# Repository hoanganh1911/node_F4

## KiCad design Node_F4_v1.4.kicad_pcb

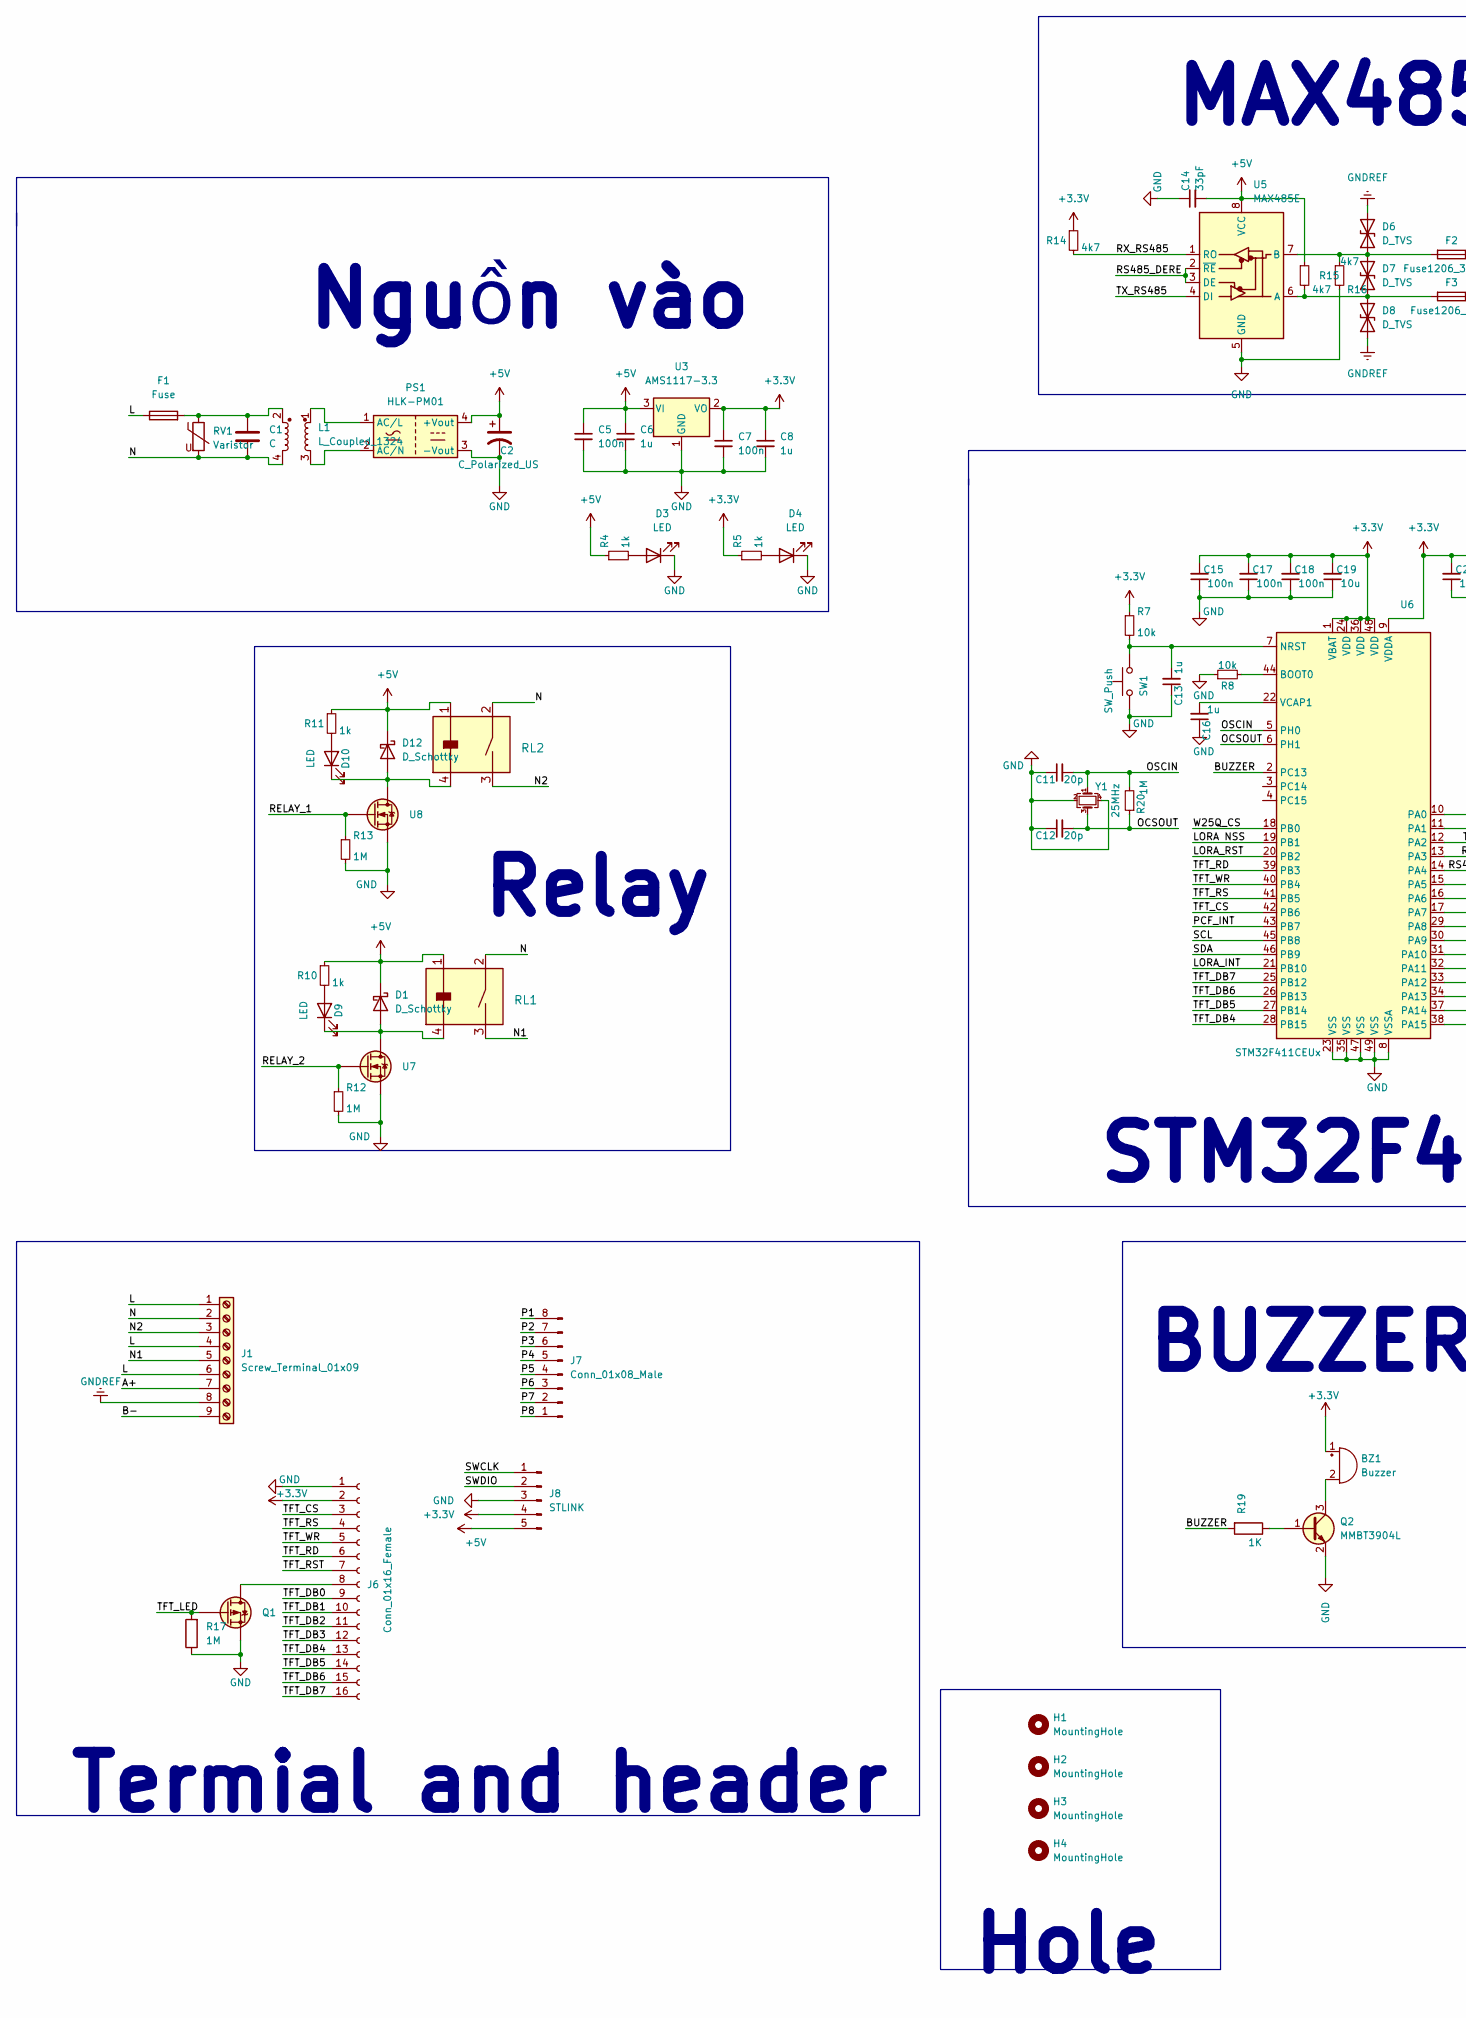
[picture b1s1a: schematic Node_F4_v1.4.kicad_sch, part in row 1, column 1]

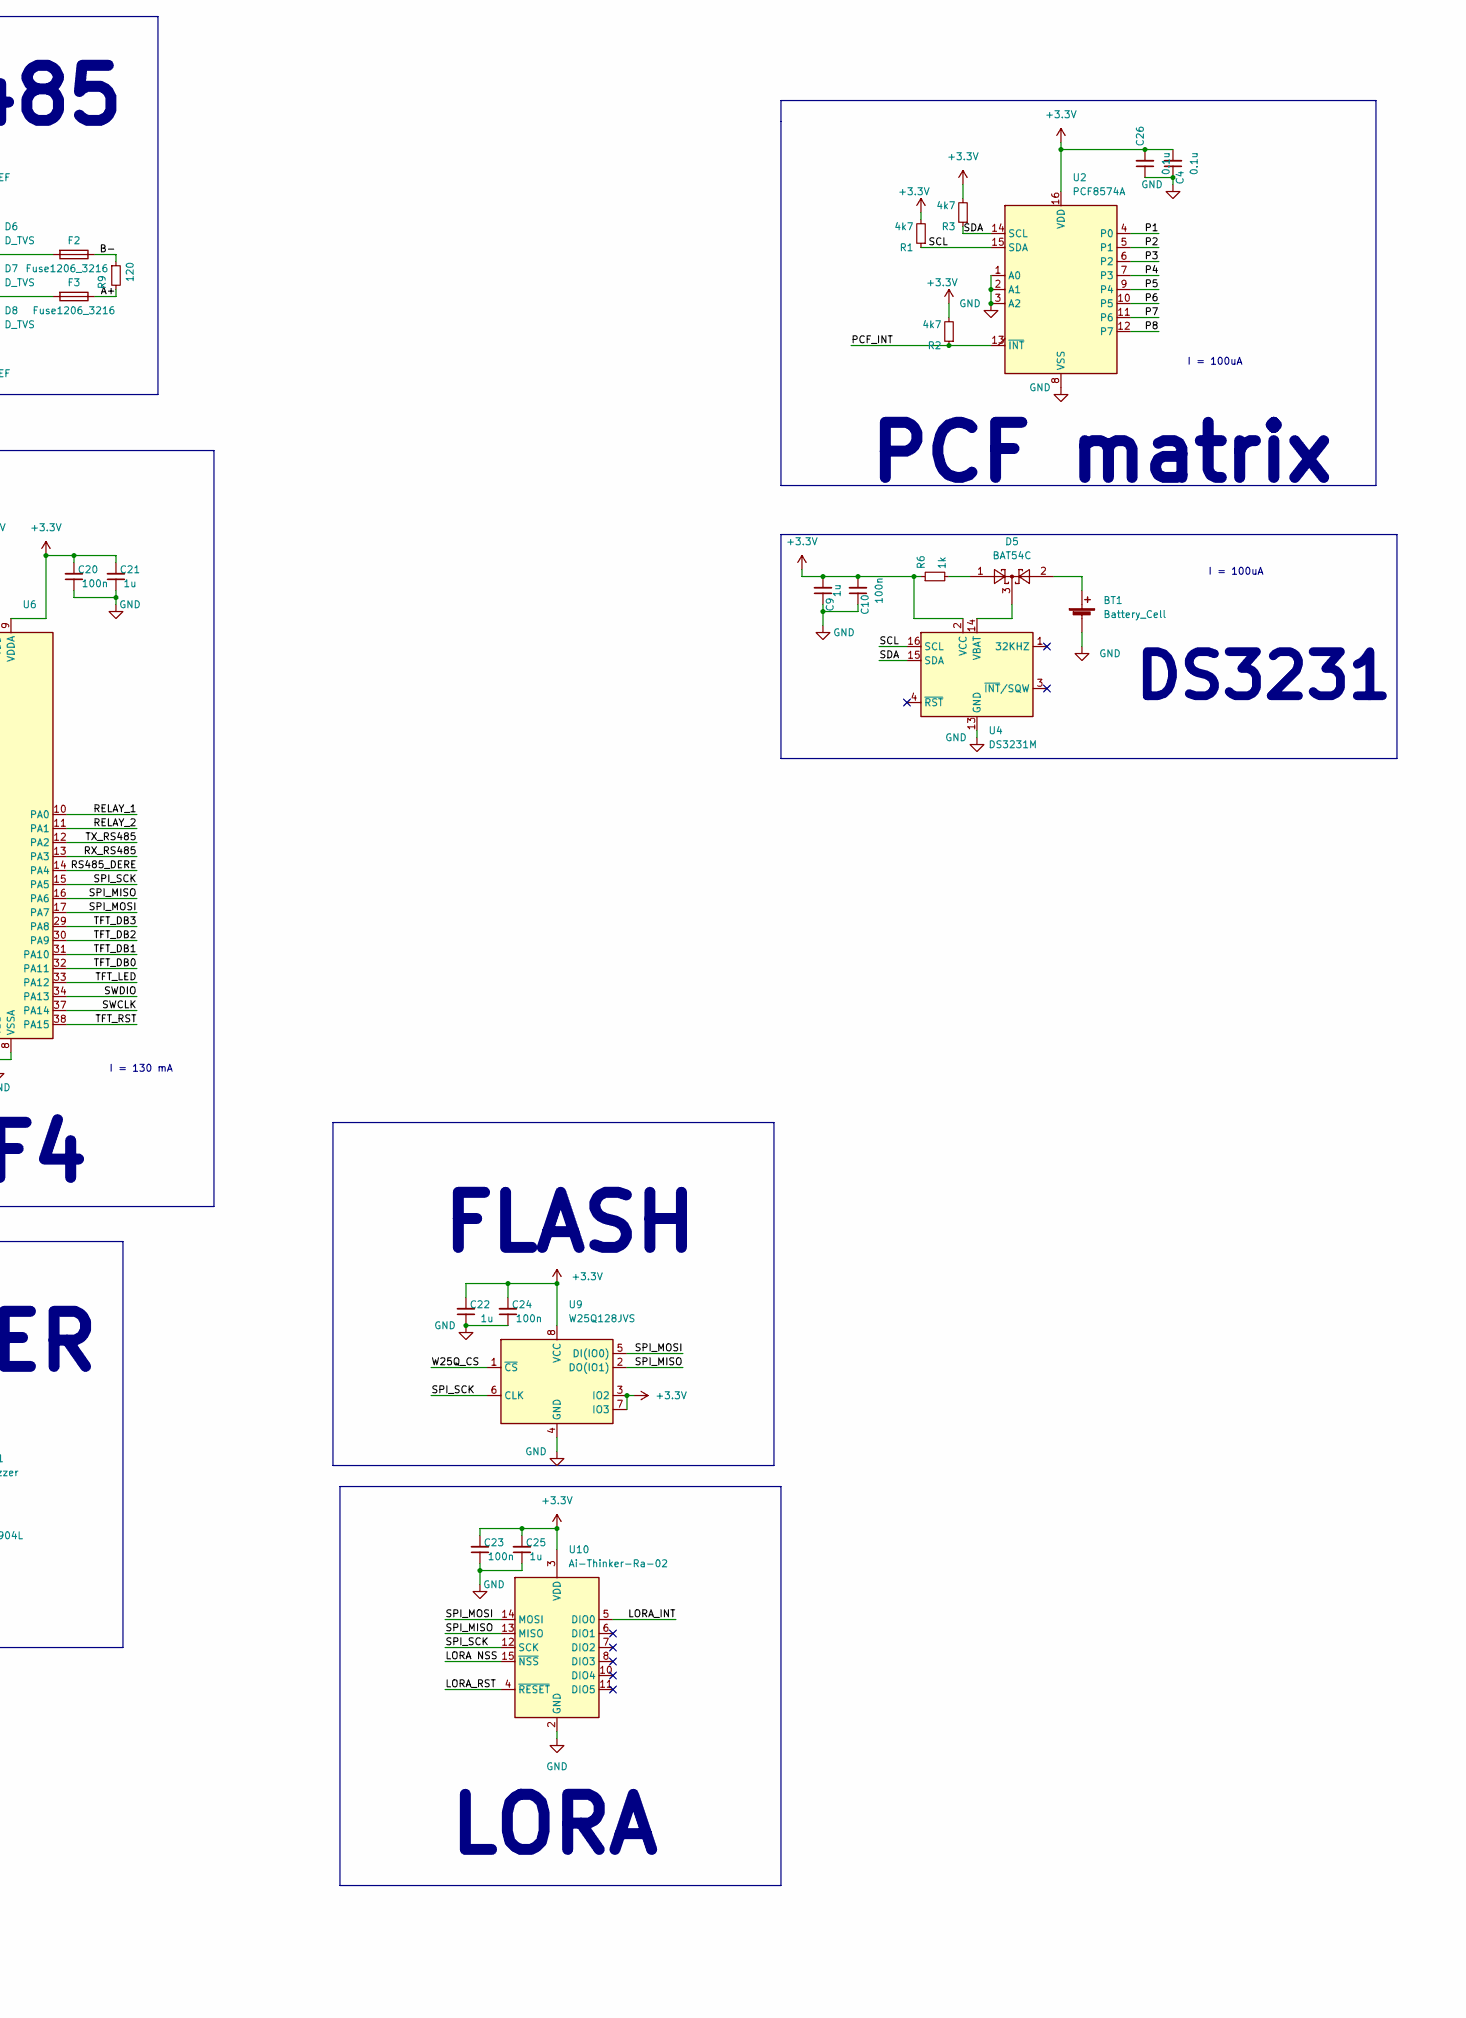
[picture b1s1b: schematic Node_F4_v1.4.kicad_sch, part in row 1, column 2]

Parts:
BT1: Battery_Cell; BatteryHolder_CR1220
BZ1: Buzzer; PUIAudio_SMT_0825_S_4_R
C1: C; C_Rect_L16.5mm_W5.0mm_P15.00mm_MKT
C2: C_Polarized_US; CP_Alu_SMD_6.3x7.7mm
C4, C26: 0.1u; C_0603_1608Metric
C5, C7, C10, C15, C17, C18, C20, C23, C24: 100n; C_0603_1608Metric
C6, C8, C9, C13, C16, C21, C22, C25: 1u; C_0603_1608Metric
C11, C12: 20p; C_0603_1608Metric
C14: 33pF; C_0603_1608Metric
C19: 10u; C_0603_1608Metric
D1, D12: D_Schottky; D_SOD-123F
D3, D4, D9, D10: LED; LED_0603_1608Metric
D5: BAT54C; SOT-23
D6, D7, D8: D_TVS; D_SMA
F1: Fuse; Fuse_BelFuse_0ZRE0075FF_L11.5mm_W4.8mm
F2, F3: Fuse1206_3216; Fuse_1206_3216Metric
H1, H2, H3, H4: MountingHole; MountingHole_2.2mm_M2_Pad_Via
J1: Screw_Terminal_01x09; TerminalBlock_Phoenix_MKDS-1,5-9_1x09_P5.00mm_Horizontal
J6: Conn_01x16_Female; PinSocket_1x16_P2.54mm_Vertical
J7: Conn_01x08_Male; PinHeader_1x08_P2.54mm_Vertical
J8: STLINK; PinHeader_1x05_P2.54mm_Vertical
L1: L_Coupled_1324; ACFilterChokeUU9.8
PS1: HLK-PM01; HLK_P01
Q1: P_Mosfet; SOT23-3
Q2: MMBT3904L; SOT23-3
R1, R2, R3, R14, R15, R16: 4k7; R_0603_1608Metric
R4, R5, R6, R10, R11: 1k; R_0603_1608Metric
R7, R8: 10k; R_0603_1608Metric
R9: 120; R_0603_1608Metric
R12, R13, R17, R20: 1M; R_0603_1608Metric
R19: 1K; R_0603_1608Metric
RL1, RL2: Relay_G5NB-1A-E_DC5; Relay_G5NB-1A-E DC5
RV1: Varistor; RV_Disc_D12mm_W5.8mm_P7.5mm
SW1: SW_Push; SW_SPST_PTS810
U2: PCF8574A; SOIC-16W_7.5x10.3mm_P1.27mm
U3: AMS1117-3.3; SOT-223-3_TabPin2
U4: DS3231M; SOIC-16W_7.5x10.3mm_P1.27mm
U5: MAX485E; SOIC-8_3.9x4.9mm_P1.27mm
U6: STM32F411CEUx; QFN-48-1EP_7x7mm_P0.5mm_EP5.6x5.6mm
U7, U8: Trans_MOSFET; SOT23-3
U9: W25Q128JVS; SOIC-8_5.23x5.23mm_P1.27mm
U10: Ai-Thinker-Ra-02; MODULE_RA-02_LORA
Y1: 25MHz; Crystal_SMD_3225-4Pin_3.2x2.5mm

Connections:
+3.3V: BZ1.1 (-), C4.2, C7.1, C8.1, C9.2, C10.2, C15.2, C17.2, C18.2, C19.2, C20.2, C21.2, C22.2, C23.2, C24.2, C25.2, C26.2, J6.2, J8.4, R1.2, R2.2, R3.2, R5.1, R6.1, R7.1, R14.1, U2.16 (VDD), U3.2 (VO), U4.2 (VCC), U6.1 (VBAT), U6.9 (VDDA), U6.24 (VDD), U6.36 (VDD), U6.48 (VDD), U9.3 (IO2), U9.7 (IO3), U9.8 (VCC), U10.3 (VDD)
+5V: C2.1, C5.1, C6.1, C14.2, D1.1 (K), D12.1 (K), J8.5, PS1.4 (+Vout), R4.1, R10.1, R11.1, R15.1, RL1.1, RL2.1, U3.3 (VI), U5.8 (VCC)
/A+: F3.1, J1.7, R9.2
/B-: F2.1, J1.9, R9.1
/BUZZER: R19.2, U6.2 (PC13)
/L: F1.1, J1.1, J1.4, J1.6
/LORA NSS: U6.19 (PB1), U10.15 (~NSS)
/LORA_INT: U6.21 (PB10), U10.5 (DIO0)
/LORA_RST: U6.20 (PB2), U10.4 (~RESET)
/N: C1.2, J1.2, L1.4, RL1.2, RL2.2, RV1.2
/N1: J1.5, RL1.3
/N2: J1.3, RL2.3
/OCSOUT: C12.2, R20.1, U6.6 (PH1), Y1.3
/OSCIN: C11.2, R20.2, U6.5 (PH0), Y1.1
/P1: J7.8, U2.4 (P0)
/P2: J7.7, U2.5 (P1)
/P3: J7.6, U2.6 (P2)
/P4: J7.5, U2.7 (P3)
/P5: J7.4, U2.9 (P4)
/P6: J7.3, U2.10 (P5)
/P7: J7.2, U2.11 (P6)
/P8: J7.1, U2.12 (P7)
/PCF_INT: R2.1, U2.13 (~INT), U6.43 (PB7)
/RELAY_1: R13.1, U6.10 (PA0), U8.1 (G)
/RELAY_2: R12.1, U6.11 (PA1), U7.1 (G)
/RS485_DERE: U5.2 (~RE), U5.3 (DE), U6.14 (PA4)
/RX_RS485: R14.2, U5.1 (RO), U6.13 (PA3)
/SCL: R1.1, U2.15 (SDA), U4.16 (SCL), U6.45 (PB8)
/SDA: R3.1, U2.14 (SCL), U4.15 (SDA), U6.46 (PB9)
/SPI_MISO: U6.16 (PA6), U9.2 (DO(IO1)), U10.13 (MISO)
/SPI_MOSI: U6.17 (PA7), U9.5 (DI(IO0)), U10.14 (MOSI)
/SPI_SCK: U6.15 (PA5), U9.6 (CLK), U10.12 (SCK)
/SWCLK: J8.1, U6.37 (PA14)
/SWDIO: J8.2, U6.34 (PA13)
/TFT_CS: J6.3, U6.42 (PB6)
/TFT_DB0: J6.9, U6.32 (PA11)
/TFT_DB1: J6.10, U6.31 (PA10)
/TFT_DB2: J6.11, U6.30 (PA9)
/TFT_DB3: J6.12, U6.29 (PA8)
/TFT_DB4: J6.13, U6.28 (PB15)
/TFT_DB5: J6.14, U6.27 (PB14)
/TFT_DB6: J6.15, U6.26 (PB13)
/TFT_DB7: J6.16, U6.25 (PB12)
/TFT_LED: Q1.1 (G), R17.2, U6.33 (PA12)
/TFT_RD: J6.6, U6.39 (PB3)
/TFT_RS: J6.4, U6.41 (PB5)
/TFT_RST: J6.7, U6.38 (PA15)
/TFT_WR: J6.5, U6.40 (PB4)
/TX_RS485: U5.4 (DI), U6.12 (PA2)
/W25Q_CS: U6.18 (PB0), U9.1 (~CS)
GND: BT1.2 (-), C2.2, C4.1, C5.2, C6.2, C7.2, C8.2, C9.1, C10.1, C11.1, C12.1, C13.1, C14.1, C15.1, C16.1, C17.1, C18.1, C19.1, C20.1, C21.1, C22.1, C23.1, C24.1, C25.1, C26.1, D3.1 (K), D4.1 (K), J6.1, J8.3, PS1.3 (-Vout), Q1.2 (S), Q2.2 (E), R8.1, R12.2, R13.2, R16.2, R17.1, SW1.1, U2.1 (A0), U2.2 (A1), U2.3 (A2), U2.8 (VSS), U3.1 (GND), U4.5 (GND), U4.6 (GND), U4.7 (GND), U4.8 (GND), U4.9 (GND), U4.10 (GND), U4.11 (GND), U4.12 (GND), U4.13 (GND), U5.5 (GND), U6.8 (VSSA), U6.23 (VSS), U6.35 (VSS), U6.47 (VSS), U6.49 (VSS), U7.2 (S), U8.2 (S), U9.4 (GND), U10.1 (GND), U10.2 (GND), U10.9 (GND), U10.16 (GND), Y1.2, Y1.4
GNDREF: D6.2 (A2), D8.1 (A1), J1.8
unnamed: BT1.1 (+), D5.2
unnamed: BZ1.2 (+), Q2.3 (C)
unnamed: C1.1, F1.2, L1.2, RV1.1
unnamed: C13.2, R7.2, SW1.2, U6.7 (NRST)
unnamed: C16.2, U6.22 (VCAP1)
unnamed: D3.2 (A), R4.2
unnamed: D4.2 (A), R5.2
unnamed: D5.1, R6.2
unnamed: D5.3, U4.14 (VBAT)
unnamed: D6.1 (A1), D7.2 (A2), F2.2, R16.1, U5.7 (B)
unnamed: D7.1 (A1), D8.2 (A2), F3.2, R15.2, U5.6 (A)
unnamed: D1.2 (A), D9.1 (K), RL1.4, U7.3 (D)
unnamed: D9.2 (A), R10.2
unnamed: D10.1 (K), D12.2 (A), RL2.4, U8.3 (D)
unnamed: D10.2 (A), R11.2
unnamed: J6.8, Q1.3 (D)
unnamed: L1.1, PS1.1 (AC/L)
unnamed: L1.3, PS1.2 (AC/N)
unnamed: Q2.1 (B), R19.1
unnamed: R8.2, U6.44 (BOOT0)

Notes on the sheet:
FLASH
I = 130 mA
LORA
I = 100uA
Hole
PCF matrix
Nguồn vào
STM32F4
Relay
DS3231
MAX485
Termial and header
BUZZER

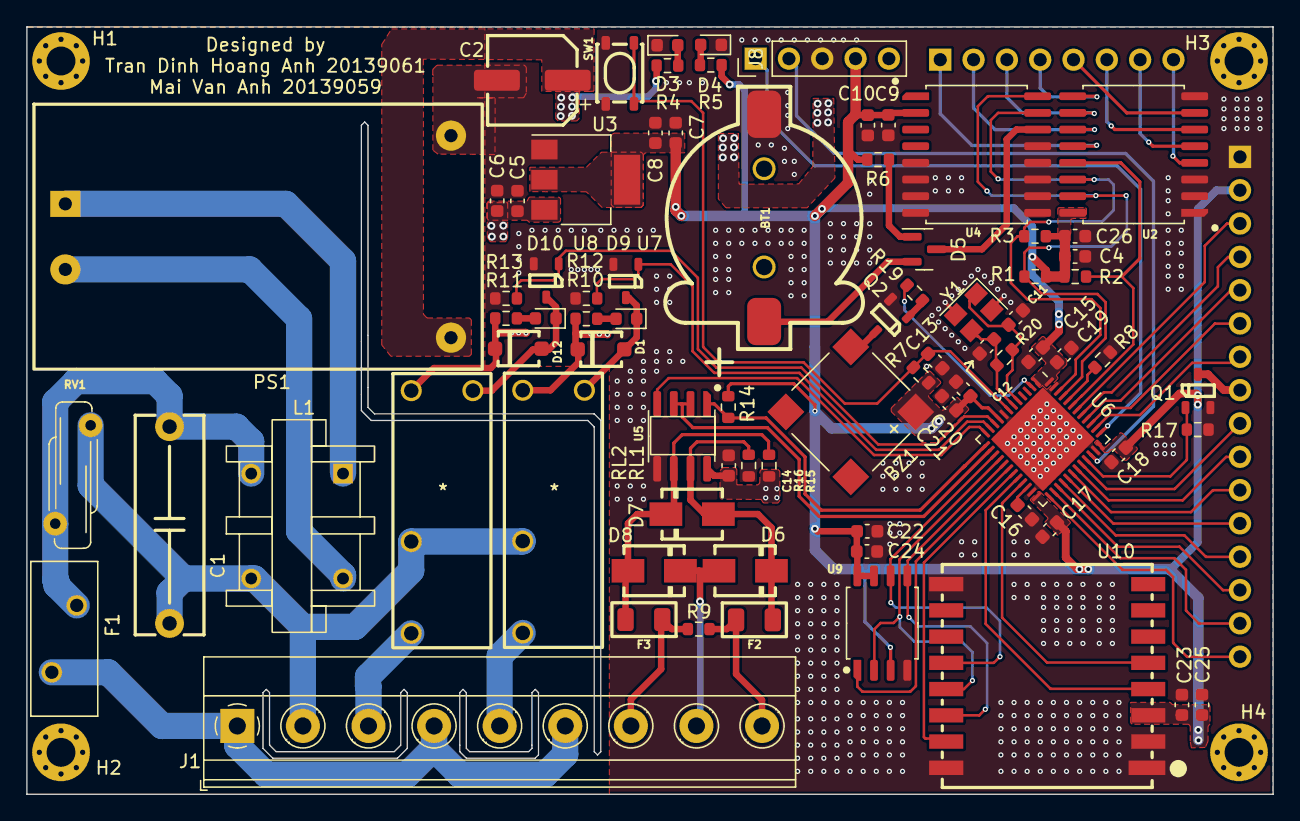
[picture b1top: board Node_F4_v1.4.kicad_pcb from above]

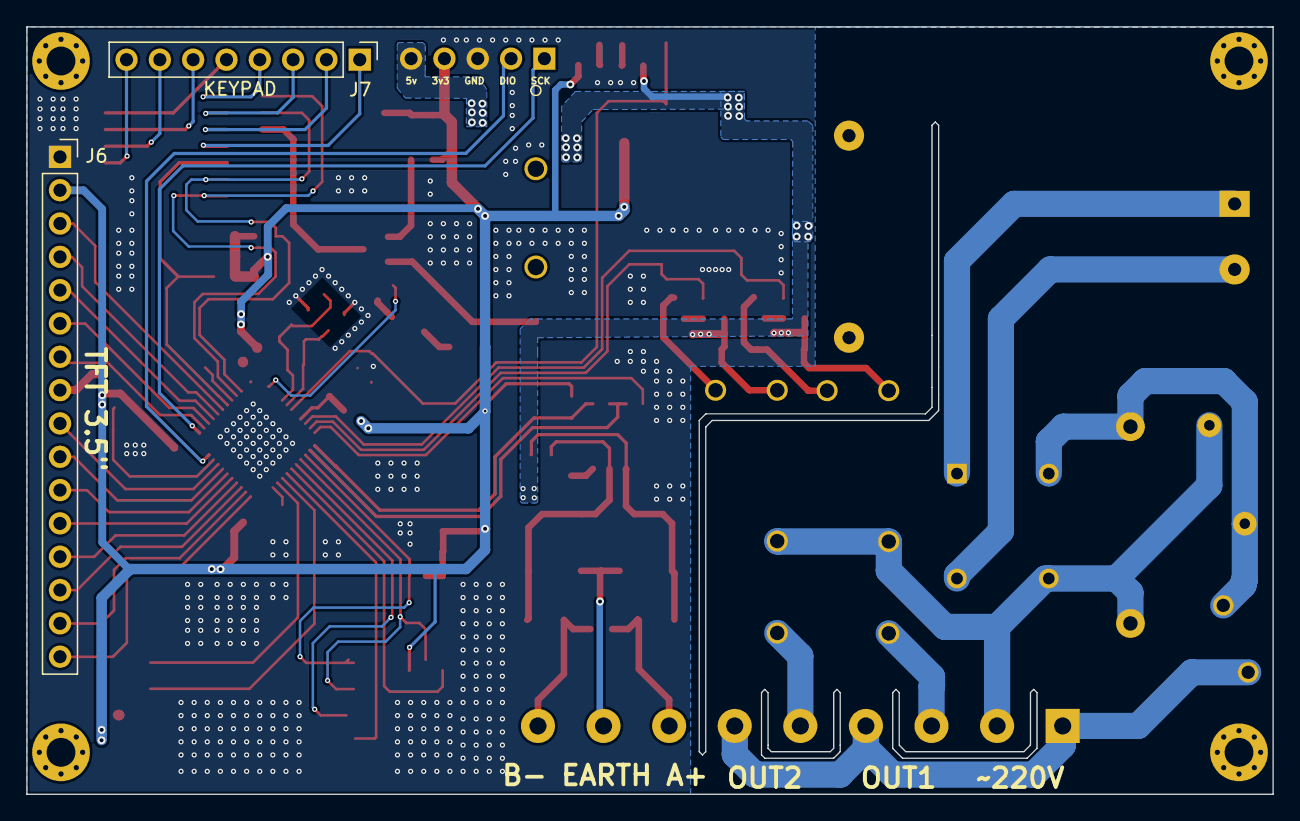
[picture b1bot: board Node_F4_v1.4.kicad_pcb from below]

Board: 2 copper layers, 95.0 x 58.5 mm, 85 parts (2 on the bottom side), 72 nets.

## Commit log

2023-03-07 sua nguon
2023-03-07 thay terminal
2023-03-07 teardrop
2023-03-07 chinh via
2023-03-09 DONE
2023-03-09 Fix GND alu cap at output HLK

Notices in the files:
parts and their libraries:
Copyright 2021 Accelerated Designs. All rights reserved.
